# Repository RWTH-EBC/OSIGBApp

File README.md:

# OSIGBApp
Open-Source Internet of Things (IoT) Gateways for Building Automation Applications

This repository will be populated in course of a journal publication (see publications section down below).

<!-- openocd -f board/esp32-wrover-kit-3.3v.cfg -->

## General

The IoT gateways are designed to operate as an interface for legacy components in building automation systems and IoT-based applications, e. g. connecting to cloud services via IoT protocols communication like MQTT. 

To this end, this repository contains the relevant [schematics and PCB design](https://github.com/RWTH-EBC/OSIGBApp/tree/main/Schematics) to obtain the interfacing hardware allowing to digitize and convert signals from sensors or to actuators. 
Here, the following signals are supported:
- Analog communication (0-10 V, 0-20 mA)
- Resistive measurements of passive RTD-probes (2,3,4-wire)
- Digital communication via RS-485/EIA-485 (for instance used in serial Modbus RTU or BACnet MS/TP communication)

Core component of the gateways is the ESP32 microcontroller.
Hence, the firmware was developed using the Espressif IoT Development Framework [ESP-IDF](https://github.com/espressif/esp-idf), which is the official development framework provided by the manufacturer for the [ESP32](https://espressif.com/en/products/hardware/esp32/overview) chip.
Accordingly, the developed [firmware](https://github.com/RWTH-EBC/OSIGBApp/tree/main/Firmware) is provided as well in this repository. 
In order to ease use and operation of the gateways, we further provide a [documentation](https://github.com/RWTH-EBC/OSIGBApp/tree/main/Documentation). 
Finally, a [performance analysis](https://github.com/RWTH-EBC/OSIGBApp/tree/main/PerformanceAnalysis) has been conducted comparing the measurement performance with a conversion via a PLC.

## Documentation:
- The user Manual "how to operate the gateways" can be found [here](Documentation/manual.pdf). 
- For using the software, [ESP-IDF](https://github.com/espressif/esp-idf) is needed. We also recommend to use [VScode](https://code.visualstudio.com/) with the ESP-IDF extension for programming.
- Furthermore, tips for using the Menuconfig with this software can be found in the Wiki of the repository.
- All functions in the code are commented and a documentation is generated with [Doxygen](https://github.com/doxygen/doxygen). The result can be found in the [DOC folder](https://github.com/RWTH-EBC/OSIGBApp/tree/main/Firmware/doc). You have to clone the repository and open doc/doxygen/html/index.html to view the complete documentation.

- Documentation on how to build the Aio Configurator webpage can be found here: [AIO Configurator](Firmware/doc/aio_configurator.md)
  - The IoT-AIO Configurator is a web page that uses HTML forms to configure the IoT Wireless Adapter.
    The source code and documentation can be obtained here:
      - [Configurator Request](Firmware/doc/markdown/aio_configurator_request.html)
      - [Configurator Response](Firmware/doc/markdown/aio_configurator_response.html)
     
- Further developement Ideas, by Carlo Guarnieri can be found here: [Developments](Firmware/doc/developments.md)

## Terms of use
All content provided in this repository is released under the [MIT License](https://github.com/RWTH-EBC/OSIGBApp/blob/main/LICENSE). 
If any of the content provided is used, please give credit by referencing the related publication, as decribed in the subsequent section.

## Publications and referencing
<!--The IoT-Gateways have been developed in several research projects between 2018 and 2021. A core development for the current state has been conducted during the Master Thesis of Kai Droste in 2020. -->
We kindly ask all publicly disseminated projects employing components of the IoT gateways to cite the following paper:

<!--  - Kai Droste "[Development of a cloud controlled building automation and comparison with the current state of the art](https://git-ce.rwth-aachen.de/ebc/projects/ebc0449_bmwi_nextgenbat_ga/iot-development/iot-development.dissemination/theses/development-of-a-cloud-controlled-building-automation-and-comparison-with-the-current-state-of-the-art)", 2020 Masterthesis   -->
- **Schraven, Markus Hans, Kai Droste, Carlo Guarnieri Calò Carducci, Dirk Müller, and Antonello Monti. 2022. "Open-Source Internet of Things Gateways for Building Automation Applications" Journal of Sensor and Actuator Networks 11, no. 4: 74. https://doi.org/10.3390/jsan11040074**

Previous development stages are documented in:
- M.H. Schraven, C. Guarnieri Calò Carducci, M.A. Baranski, D. Mueller, A. Monti, “Designing a Development Board for Research on IoT Appli-cations in Building Automation Systems,” 36th International Symposiumon  Automation  and  Robotics  in  Construction  (ISARC  2019),  Banff,Canada, 2019, pp. 82-90, [DOI: 10.22260/ISARC2019/0012](https://doi.org/10.22260/ISARC2019/0012)
- C. Guarnieri Calò Carducci, A. Monti, M. H. Schraven, M. Schumacher and D. Mueller, “Enabling ESP32-based IoT Applications in Building Automation Systems,” 2019 II Workshop on Metrology for Industry 4.0 and IoT (MetroInd4.0&IoT), Naples, Italy, 2019, pp. 306-311, [DOI: 10.1109/METROI4.2019.8792852](https://doi.org/10.1109/METROI4.2019.8792852)

# Further software related to IoT-AIO

## IoT-AIO Configurator

# Contact

- [Kai Droste](mailto:kai.droste@eonerc.rwth-aachen.de)
- [Markus Schraven](mailto:mschrave@eonerc.rwth-aachen.de)
- [Carlo Guarnieri](mailto:cguarnieri@eonerc.rwth-aachen.de)

[EON Energy Research Center (EONERC)](http://www.eonerc.rwth-aachen.de)  
[Institute for Automation of Complex Power Systems (ACS)](http://www.acs.eonerc.rwth-aachen.de)  
[RWTH University Aachen, Germany](http://www.rwth-aachen.de)

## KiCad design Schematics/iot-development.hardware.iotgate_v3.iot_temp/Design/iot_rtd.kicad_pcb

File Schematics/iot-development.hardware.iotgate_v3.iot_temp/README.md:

# iot_temp

This repository entails the specifications and PCB design of a gateway communicating with temperature sensors.

**Specifications:**
*  Battery: LiFePo4 18650 cell [lipopower.de](https://shop.lipopower.de/A123-Systems-APR18650M1A-1100mAh)
    * Battery holder: [Datasheet](Datasheet/Keystone_01142020_1042.pdf)
*  Case dimensions: 120 x 75 x 36 mm 
    *  Case Datasheet: [Spelsberg 2K-16](Datasheet/M-346-916-01_V1.pdf)

[Drawing](Datasheet\temp-drawing.pdf)

* ESP32-WROOM-32D
* Header Pins for flashing bridge 
    * [ESP-Prog](https://github.comespressif/esp-iot-solution/blob/master/documentsevaluation_boards/ESP-Prog_guide_en.md)
* Reset Button (EN)
* 2x MAX31865 for 2 RTD-Elements
* TS3A44159PWR Multiplexer for switching between PLC and ESP32
    * [Mouser-Link](https://www.mouser.de/ProductDetail/Texas-Instruments/TS3A44159PWR?qs=sGAEpiMZZMvjbjwkTuU2aTxU6YamLMpeYsaiusRAsW8=)
* Terminal block 18 TB004-508-18BE 
    * [Mouser-Link](https://www.mouser.de/ProductDetail/CUI-Devices/TB004-508-18BE?qs=%2Fha2pyFaduiuF0vDuq7AnN9%2FDe5hgHOKWwquf%252BQh13fOlF3uCj6rv1tKdfXqNkzP)

**IOs:**
1. Lead 1 RTD 1 (from RTD to Gateway) 
2. Lead 2 RTD 1 (from RTD to Gateway)
3. Lead 3 RTD 1 (from RTD to Gateway)
4. Lead 4 RTD 1 (from RTD to Gateway)
5. Lead 1 RTD 2 (from RTD to Gateway)
6. Lead 2 RTD 2 (from RTD to Gateway)
7. Lead 3 RTD 2 (from RTD to Gateway)
8. Lead 4 RTD 2 (from RTD to Gateway)
9. Lead 1 RTD 1 (from RTD forwarding to PLC) 
10. Lead 2 RTD 1 (from RTD forwarding to PLC)
11. Lead 3 RTD 1 (from RTD forwarding to PLC)
12. Lead 4 RTD 1 (from RTD forwarding to PLC)
13. Lead 1 RTD 2 (from RTD forwarding to PLC)
14. Lead 2 RTD 2 (from RTD forwarding to PLC)
15. Lead 3 RTD 2 (from RTD forwarding to PLC)
16. Lead 4 RTD 2 (from RTD forwarding to PLC)
17. GND (input for relais switch from PLC)
18. 24 VDC (input for relais switch from PLC)

## TODO:
- [x] Housing for Battery and Board
	- [x] Measurements
	- [x] Mounting Holes

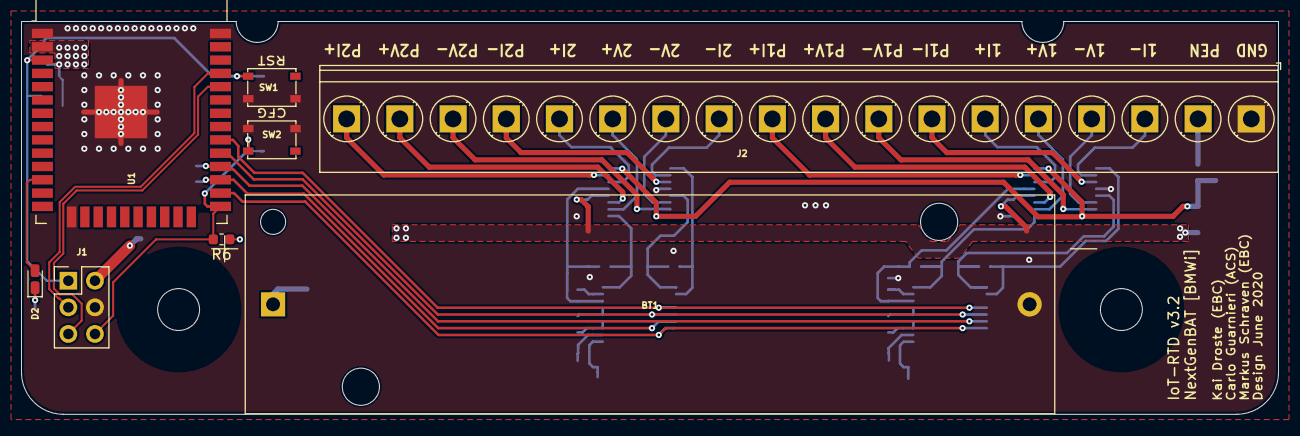
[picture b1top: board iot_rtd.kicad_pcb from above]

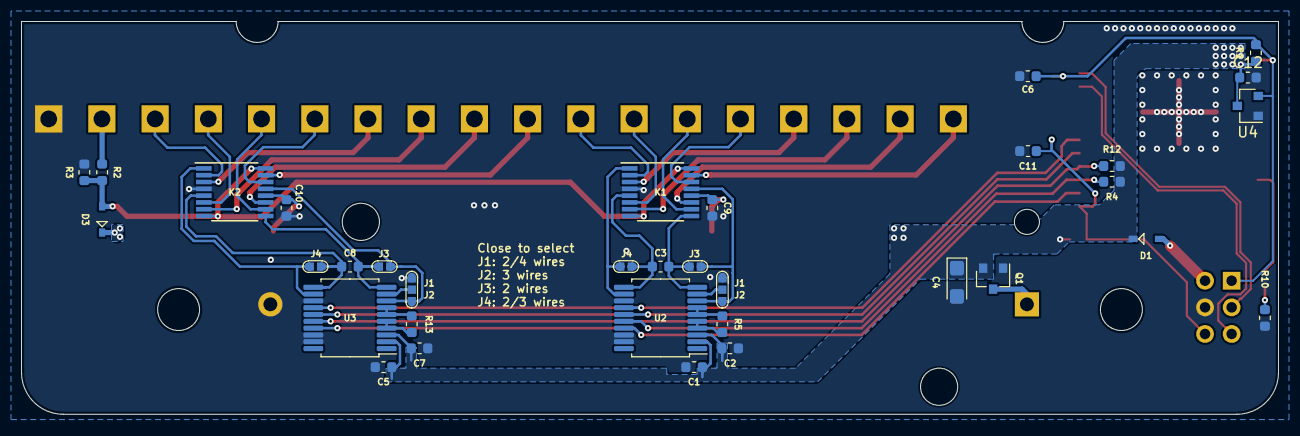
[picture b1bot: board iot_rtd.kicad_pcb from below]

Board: 2 copper layers, 120.0 x 37.5 mm, 42 parts (34 on the bottom side), 47 nets.

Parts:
BT1: LiFePo4 18650; BatteryHolder_Keystone_1043_1x18650
C1, C2, C5, C6, C7, C9, C10, C11, C12: 100n; C_0603_1608Metric
C3, C8: 1u; C_0603_1608Metric
C4: 10u; CP_EIA-3216-18_Kemet-A
D1, D3: BAT60A
D2: 150060RS75000; LED_0603_1608Metric_Castellated
J1: Conn_02x03; PinHeader_2x03_P2.54mm_Vertical
J2: TB004-508-18
JP1, JP4: Wires; SolderJumper-3_P1.1mm_Open_RoundedPad0.8x0.9mm
JP2, JP3, JP5, JP6: Wires; SolderJumper-2_P1.1mm_Open_RoundedPad0.8x0.9mm
K1, K2: TS3A44159; TSSOP-16_4.4x5mm_P0.65mm
Q1: Si2323; SOT-23
R1, R6: 10k; R_0603_1608Metric
R2: 6.8k; R_0603_1608Metric
R3: 1k; R_0603_1608Metric
R4, R12: 3.3k; R_0603_1608Metric
R5, R13: 402 0.1%; R_0603_1608Metric
R10: 270; R_0603_1608Metric
SW1, SW2: PTS815
U1: ESP32-WROOM-32D
U2, U3: MAX31865; SSOP-20_5.3x7.2mm_P0.65mm
U4: TLV803S; SOT-23

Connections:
+3V3: C1.2, C2.2, C4.1, C5.2, C7.2, C9.2, C10.2, C12.1, D1.1, D3.1, K1.12, K2.12, Q1.2, R1.1, R4.1, R6.1, R12.1, U1.2, U2.2, U2.3, U3.2, U3.3, U4.3
/1_I+: J2.6, K2.14
/1_I-: J2.3, K2.2
/1_V+: J2.5, K2.10
/1_V-: J2.4, K2.6
/2_I+: J2.14, K1.14
/2_I-: J2.11, K1.2
/2_V+: J2.13, K1.10
/2_V-: J2.12, K1.6
/ESP_1I+: JP4.3, JP5.1, K2.13, U3.8
/ESP_1I-: JP6.2, K2.1, U3.12
/ESP_1V+: C8.1, JP5.2, K2.9, U3.10
/ESP_1V-: C8.2, JP6.1, K2.5, U3.11
/ESP_2I+: JP1.3, JP2.1, K1.13, U2.8
/ESP_2I-: JP3.2, K1.1, U2.12
/ESP_2V+: C3.1, JP2.2, K1.9, U2.10
/ESP_2V-: C3.2, JP3.1, K1.5, U2.11
/ESP_CS1: R12.2, U1.28, U3.16
/ESP_CS2: R4.2, U1.27, U2.16
/ESP_DBG: D2.2, U1.12
/ESP_EN: C6.1, J1.1, R1.2, SW1.1, U1.3, U4.2
/ESP_IO0: C11.1, J1.6, R6.2, SW2.1, U1.25
/ESP_RXD: J1.5, U1.34
/ESP_SCK: U1.29, U2.15, U3.15
/ESP_SDI: U1.30, U2.14, U3.14
/ESP_SDO: U1.26, U2.17, U3.17
/ESP_TXD: J1.3, U1.35
/PLC_1I+: J2.10, K2.15
/PLC_1I-: J2.7, K2.3
/PLC_1V+: J2.9, K2.11
/PLC_1V-: J2.8, K2.7
/PLC_2I+: J2.18, K1.15
/PLC_2I-: J2.15, K1.3
/PLC_2V+: J2.17, K1.11
/PLC_2V-: J2.16, K1.7
/PLC_EN: J2.2, R2.1
/PLC_ENX: D3.2, K1.8, K1.16, K2.8, K2.16, R2.2, R3.1
GND: BT1.2, C1.1, C2.1, C4.2, C5.1, C6.2, C7.1, C9.1, C10.1, C11.2, C12.2, J1.4, J2.1, JP1.1, JP4.1, K1.4, K2.4, Q1.1, R3.2, R10.2, SW1.2, SW2.2, U1.1, U1.15, U1.38, U1.39, U2.13, U2.18, U2.19, U3.13, U3.18, U3.19, U4.1
unnamed: BT1.1, Q1.3
unnamed: D2.1, R10.1
unnamed: JP1.2, U2.9
unnamed: JP4.2, U3.9
unnamed: R5.1, U2.4, U2.5
unnamed: R5.2, U2.6, U2.7
unnamed: R13.1, U3.4, U3.5
unnamed: R13.2, U3.6, U3.7
VCOM: D1.2, J1.2

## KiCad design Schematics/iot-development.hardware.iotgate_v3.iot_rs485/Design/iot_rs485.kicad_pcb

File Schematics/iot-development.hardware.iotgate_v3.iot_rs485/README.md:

# iot_rs485

This repository entails the specifications and PCB design of a gateway communicating with devices via Modbus RTU or BACnet MS/TP.

**Specifications:**
*  Battery: None
*  Case:
    * [Datasheet](Datasheet/M-2K-12_V1.pdf)
    * outer dimensions: 85 x 85 x 37 mm 
    * inner dimensions: 73 x 73 x 25 mm
    * [PCB-Measurements:](Datasheet/Junction-Box-PCB.pdf) 75 x 40 x 1.6 mm 

*  Components: 
    * ESP32-WROOM-32D(16MB)
    * Header Pins for flashing bridge [ESP-Prog](https://github.com/espressif/esp-iot-solution/blob/master/documents/evaluation_boards/ESP-Prog_guide_en.md)
    * UART TTL to RS485 converter (Maybe BACnet needs an own gateway with a card reader? Needs to be tested)
        * Modbus-RTU
        * BACnet MS/TP
*  Additional components:
    * Double relay switch
    * Connector: 9 Position Screw Terminal 
        * [TB001-500-09BE](https://www.mouser.de/ProductDetail/CUI-Devices/TB001-500-09BE?qs=sGAEpiMZZMvPvGwLNS671%2FDanv8Jav06pFwBruE7rNiHV5dcUdCoOg%3D%3D)
        * [Datasheet](Datasheet/tb001-500-1550615.pdf)

*  IOs:
1. 24 VDC (input, supply gateway)
2. GND (input, supply gateway)
3. 24 VDC (output, supply sensor/actuator device)
4. GND (output, supply sensor/actuator device)
5. M+ (Bus signal from sensor/actuator device)
6. M- (Bus signal from sensor/actuator device)
7. M+ (Bus signal to sensor/actuator device forwarding from PLC)
8. M- (Bus signal to sensor/actuator device forwarding from PLC)
9. 24 VDC (input for relay switch from PLC)

## TODO:

- [ ] Testing BACnet.

## Example board layout:

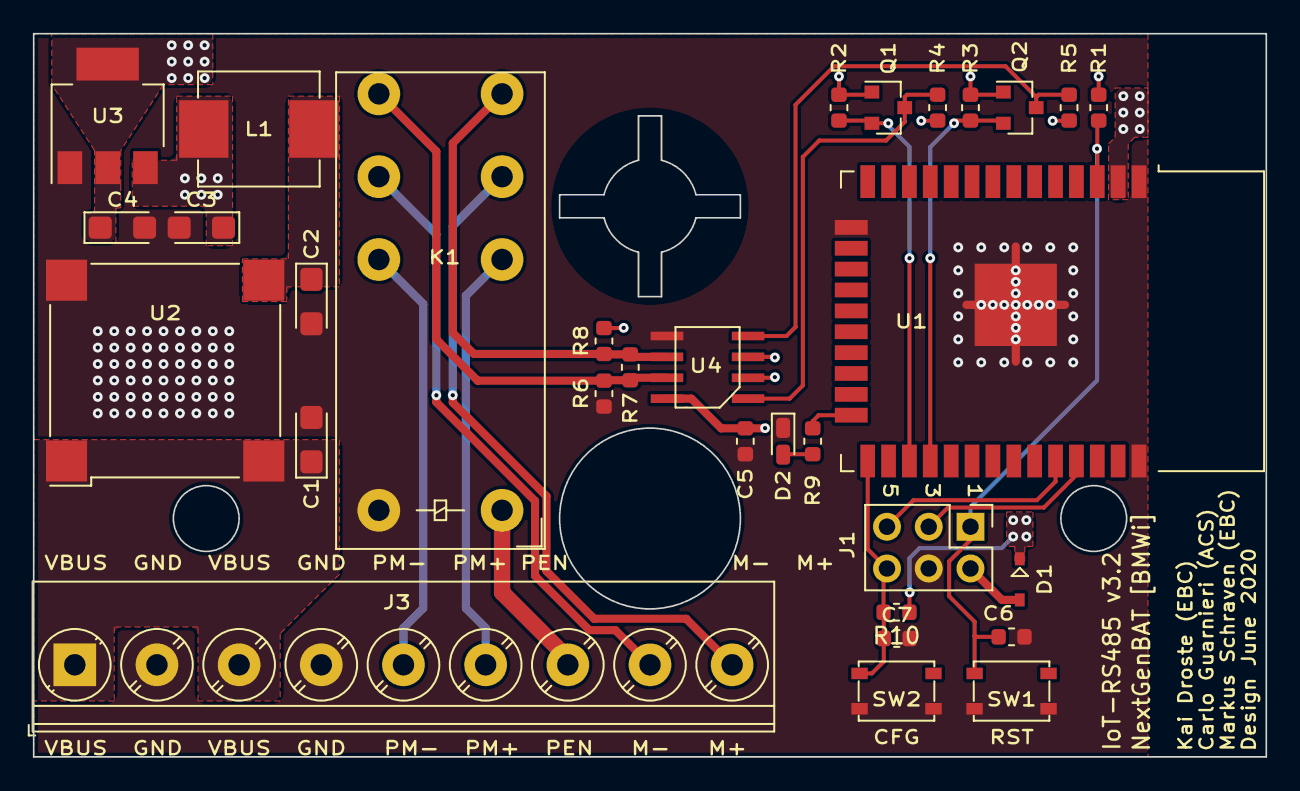
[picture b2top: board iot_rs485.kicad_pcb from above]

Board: 2 copper layers, 75.0 x 44.0 mm, 31 parts (0 on the bottom side), 23 nets.

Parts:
C1, C4: 10u; CP_EIA-3216-18_Kemet-A
C2, C3: 22u; CP_EIA-3216-18_Kemet-A
C5, C6, C7: 100n; C_0603_1608Metric
D1: BAT60A
D2: 150060RS75000; LED_0603_1608Metric_Castellated
J1: Conn_02x03; PinHeader_2x03_P2.54mm_Vertical
J3: Conn_01x09; TerminalBlock_CUI
K1: RT424024; Relay_DPDT_RT424024
L1: 22u; HM72L-0630
Q1, Q2: 2N7002; SOT-23
R1, R2, R3, R4, R5, R10: 10k; R_0603_1608Metric
R6, R8: 220; R_0603_1608Metric
R7: 120; R_0603_1608Metric
R9: 270; R_0603_1608Metric
SW1, SW2: PTS815
U1: ESP32-WROOM-32D
U2: VXO7805-500-M; VXO78-500-M
U3: AZ1117IH-3.3; SOT-223-3_TabPin2
U4: MAX13487

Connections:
+3V3: C4.1, D1.1, Q1.1, Q2.1, R1.1, R2.1, R3.1, R10.1, U1.2, U3.2
+5V: C3.1, C5.1, L1.2, R4.2, R5.1, R8.1, U3.3, U4.2, U4.3, U4.8
/ESP_DBG: R9.1, U1.24
/ESP_EN: C6.1, J1.1, R1.2, SW1.1, U1.3
/ESP_IO0: C7.1, J1.6, R10.2, SW2.1, U1.25
/ESP_M+: K1.24, R7.1, R8.2, U4.6
/ESP_M-: K1.14, R6.1, R7.2, U4.7
/ESP_RXD: J1.5, U1.34
/ESP_RXD2: Q1.2, R2.2, U1.27
/ESP_TXD: J1.3, U1.35
/ESP_TXD2: Q2.2, R3.2, U1.28
/M+: J3.9, K1.21
/M-: J3.8, K1.11
/PLC_M+: J3.6, K1.22
/PLC_M-: J3.5, K1.12
/~PLC_EN: J3.7, K1.A2
GND: C1.2, C2.2, C3.2, C4.2, C5.2, C6.2, C7.2, D2.1, J1.4, J3.2, J3.4, K1.A1, R6.2, SW1.2, SW2.2, U1.1, U1.15, U1.38, U1.39, U2.2, U3.1, U4.5
unnamed: C2.1, L1.1, U2.3
unnamed: D2.2, R9.2
unnamed: Q1.3, R4.1, U4.1
unnamed: Q2.3, R5.2, U4.4
VBUS: C1.1, J3.1, J3.3, U2.1, U2.4
VCOM: D1.2, J1.2

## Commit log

2022-07-27 Add folder structure to be filled with content
2022-09-01 initial push of the data
2022-09-01 update documentation
2022-09-01 update readme files
2022-09-07 update files for flashing the temperature gw
2022-10-11 Add scripts and data files of the performance analysis
